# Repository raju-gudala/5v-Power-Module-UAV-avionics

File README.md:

# 5V Power Module for UAV Avionics

High-efficiency, wide-input 5V DC-DC power module designed for UAV avionics, supporting 3S–12S LiPo battery input using the LT8645SHV-2 synchronous buck converter.

## Overview

Flight-critical avionics — flight controllers, GPS, telemetry modules, and onboard sensors — need clean, stable power regardless of battery state or LiPo cell count. This module was designed to deliver a regulated 5V rail across a wide input range, with protection and monitoring features built in to keep avionics powered reliably through the full flight envelope.

## Key Features

- **Wide input range** — supports 3S–12S LiPo battery configurations
- **High-efficiency conversion** — built around the LT8645SHV-2 synchronous buck converter
- **Reverse-polarity protection** — prevents damage from incorrect battery connection
- **Under-voltage lockout (UVLO)** — disables output below a safe input threshold
- **Soft-start** — controlled ramp-up to avoid inrush current stress
- **Power-good monitoring** — provides a status signal for downstream system health checks
- **Low-EMI, low-ripple layout** — optimized PCB layout to minimize output ripple and electromagnetic interference
- **Thermal optimization** — layout tuned for improved thermal performance under sustained load

## Design Details

| Parameter | Value |
|---|---|
| Input voltage range | 3S–12S LiPo (~11.1V–50.4V) |
| Output voltage | 5V regulated |
| Converter IC | LT8645SHV-2 (synchronous buck) |
| Protection | Reverse-polarity, UVLO, soft-start |
| Monitoring | Power-good signal |
| Target loads | Flight controller, GPS, telemetry, onboard sensors |

## Tools Used

- **KiCad** — schematic capture and PCB layout
- **LTspice** — circuit simulation and power stage verification

## Design Process

1. Schematic capture around the LT8645SHV-2 buck converter topology
2. Component selection for wide input range and target efficiency
3. LTspice simulation to verify power stage behavior, ripple, and transient response
4. PCB layout optimized for low EMI, low output ripple, and thermal performance
5. Protection circuit integration (reverse-polarity, UVLO, soft-start, power-good)

## Repository Contents

```
├── schematics/     # KiCad schematic files
├── pcb/             # KiCad PCB layout files
├── simulation/      # LTspice simulation files
├── gerbers/          # Fabrication-ready Gerber files
└── docs/             # Datasheets, design notes, test results
```

*(Adjust the folder structure above to match what you actually push.)*

## Status

Designed as part of UAV avionics hardware development at TiHAN-IIT Hyderabad.

## Contact

- **Raju Gudala**
- Email: rajugudala730@gmail.com
- LinkedIn: [raju-gudala](https://www.linkedin.com/in/raju-gudala)
- Portfolio: [raju-gudala.github.io](https://raju-gudala.github.io/)

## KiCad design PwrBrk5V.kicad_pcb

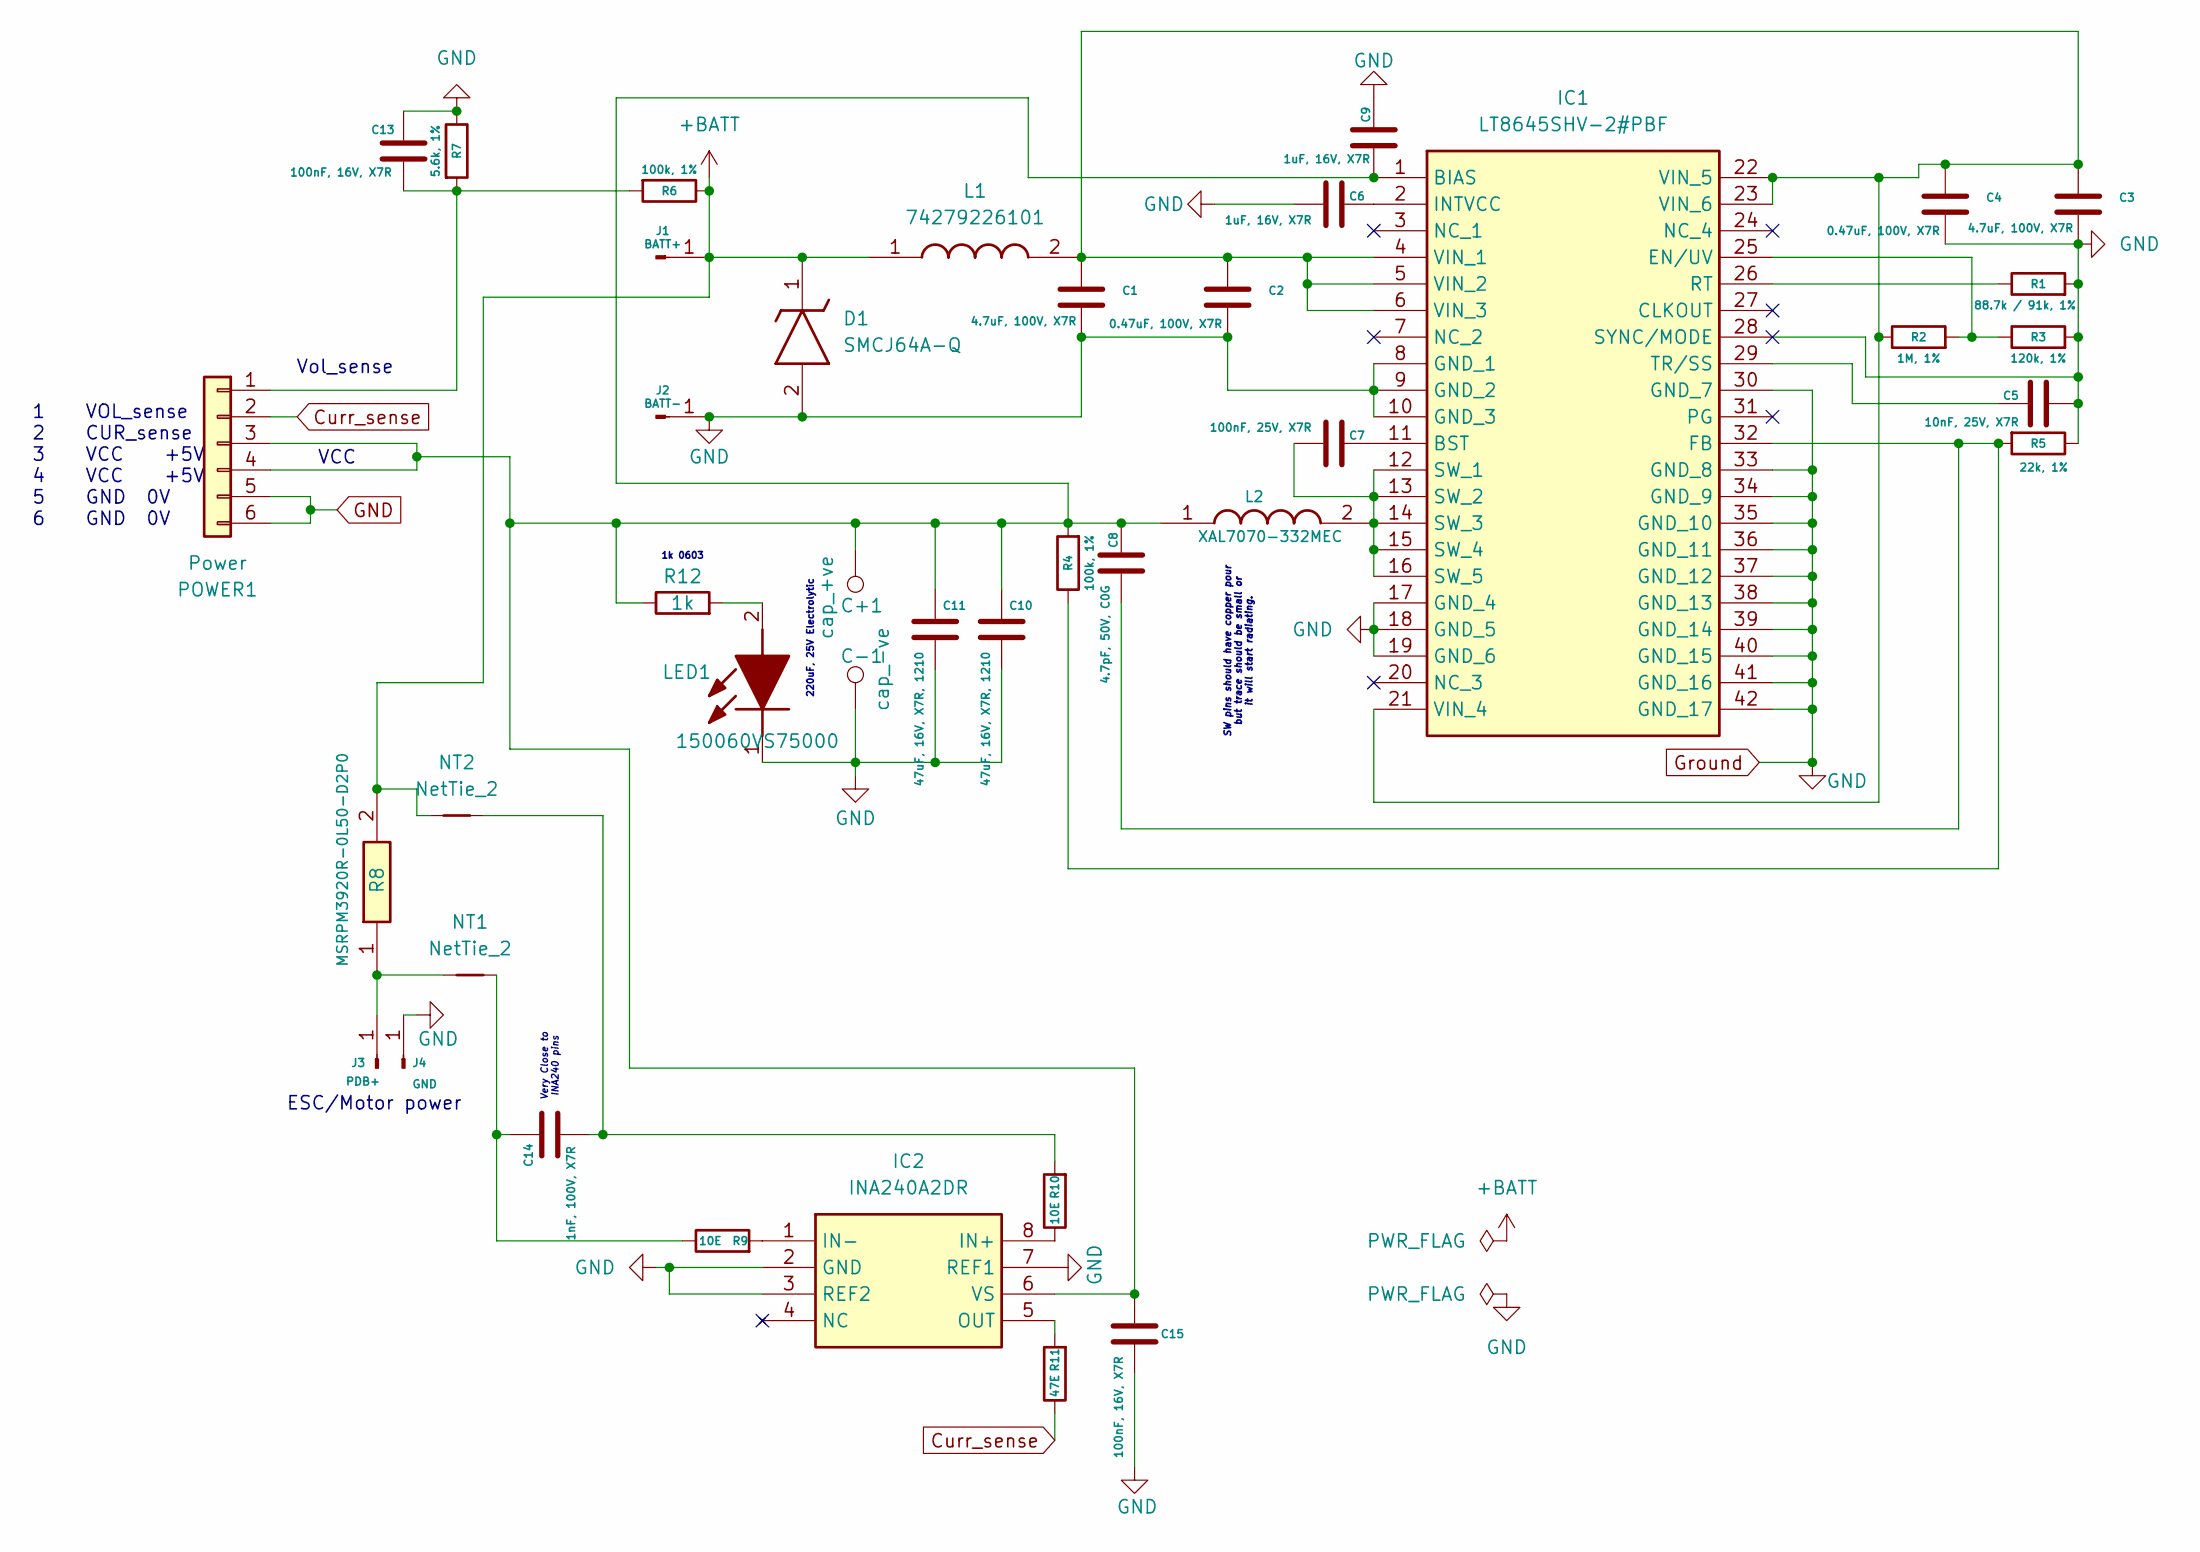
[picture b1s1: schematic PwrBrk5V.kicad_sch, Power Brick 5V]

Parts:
C1, C3: 4.7uF, 100V, X7R; C_1210_3225Metric
C2, C4: 0.47uF, 100V, X7R; C_0805_2012Metric
C5: 10nF, 25V, X7R; C_0603_1608Metric
C6, C9: 1uF, 16V, X7R; C_0603_1608Metric
C7: 100nF, 25V, X7R; C_0603_1608Metric
C8: 4.7pF, 50V, C0G; C_0603_1608Metric
C10, C11: 47uF, 16V, X7R, 1210; C_1210_3225Metric
C13: 100nF, 16V, X7R; R_0603_1608Metric
C14: 1nF, 100V, X7R; C_0603_1608Metric
C15: 100nF, 16V, X7R; C_0603_1608Metric
C+1: cap_+ve; solder_pad_2.5mmx2.5mm
C-1: cap_-ve; solder_pad_2.5mmx2.5mm
D1: SMCJ64A-Q; DIOM7959X262N; Mouser Part Number 652-SMCJ64A-Q
IC1: LT8645SHV-2#PBF; LT8645SHV2PBF; Mouser Part Number 584-LT8645SHV-2#PBF
IC2: INA240A2DR; SOIC127P600X175-8N; Mouser Part Number 595-INA240A2DR
J1: BATT+; pad 7mmx7mm
J2: BATT-; pad 7mmx7mm
J3: PDB+; pad 7mmx7mm
J4: GND; pad 7mmx7mm
L1: 74279226101; WE-MPSB_181252; Mouser Part Number 710-74279226101
L2: XAL7070-332MEC; XAL7070332MEC; Mouser Part Number 994-XAL7070-332MEC
LED1: 150060VS75000; LEDC1608X70N; Mouser Part Number 710-150060VS75000
NT1, NT2: NetTie_2; NetTie-2_SMD_Pad0.5mm
POWER1: Power; SM06B-GHS-TB
R1: 88.7k / 91k, 1%; R_0603_1608Metric
R2: 1M, 1%; R_0603_1608Metric
R3: 120k, 1%; R_0603_1608Metric
R4: 100k, 1%; R_0603_1608Metric
R5: 22k, 1%; R_0603_1608Metric
R6: 100k, 1%; R_0805_2012Metric
R7: 5.6k, 1%; R_0603_1608Metric
R8: MSRPM3920R-0L50-D2P0; MSRPM3920R0L50D2P0; Manufacturer_Part_Number MSRPM3920R-0L50-D2P0
R9, R10: 10E; R_0603_1608Metric
R11: 47E; R_0603_1608Metric
R12: 1k; R_0603_1608Metric

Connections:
+BATT: D1.1 (K), J1.1 (Pin_1_1), L1.1, NT2.1, R6.1, R8.2
Curr_sense: POWER1.2, R11.1
GND: C1.2, C2.2, C3.2, C4.2, C5.2, C6.1, C9.2, C10.1, C11.1, C13.2, C15.1, C-1.1 (1_1), D1.2 (A), IC1.8 (GND_1), IC1.9 (GND_2), IC1.10 (GND_3), IC1.17 (GND_4), IC1.18 (GND_5), IC1.19 (GND_6), IC1.28 (SYNC/MODE), IC1.30 (GND_7), IC1.33 (GND_8), IC1.34 (GND_9), IC1.35 (GND_10), IC1.36 (GND_11), IC1.37 (GND_12), IC1.38 (GND_13), IC1.39 (GND_14), IC1.40 (GND_15), IC1.41 (GND_16), IC1.42 (GND_17), IC2.2 (GND), IC2.3 (REF2), IC2.7 (REF1), J2.1 (Pin_1_1), J4.1 (Pin_1_1), LED1.1 (K), POWER1.5, POWER1.6, R1.2, R3.2, R5.1, R7.1
unnamed: C14.1, NT2.2, R10.2
unnamed: C14.2, NT1.2, R9.1
unnamed: C8.2, C9.1, C10.2, C11.2, C15.2, C+1.1 (1_1), IC1.1 (BIAS), IC2.6 (VS), L2.1, POWER1.3, POWER1.4, R4.2, R12.1
unnamed: C7.2, IC1.11 (BST)
unnamed: IC1.25 (EN/UV), R2.2, R3.1
unnamed: C8.1, IC1.32 (FB), R4.1, R5.2
unnamed: C6.2, IC1.2 (INTVCC)
unnamed: IC1.26 (RT), R1.1
unnamed: C7.1, IC1.12 (SW_1), IC1.13 (SW_2), IC1.14 (SW_3), IC1.15 (SW_4), IC1.16 (SW_5), L2.2
unnamed: C5.1, IC1.29 (TR/SS)
unnamed: C1.1, C2.1, C3.1, C4.1, IC1.4 (VIN_1), IC1.5 (VIN_2), IC1.6 (VIN_3), IC1.21 (VIN_4), IC1.22 (VIN_5), IC1.23 (VIN_6), L1.2, R2.1
unnamed: IC2.8 (IN+), R10.1
unnamed: IC2.1 (IN-), R9.2
unnamed: IC2.5 (OUT), R11.2
unnamed: J3.1 (Pin_1_1), NT1.1, R8.1
unnamed: LED1.2 (A), R12.2
unnamed: C13.1, POWER1.1, R6.2, R7.2

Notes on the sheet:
1k 0603
SW pins should have copper pour but trace should be small or it will start radiating.
1 VOL_sense 2 CUR_sense 3 VCC +5V 4 VCC +5V 5 GND 0V 6 GND 0V
220uF, 25V Electrolytic
ESC/Motor power
VCC
Vol_sense
Very Close to INA240 pins

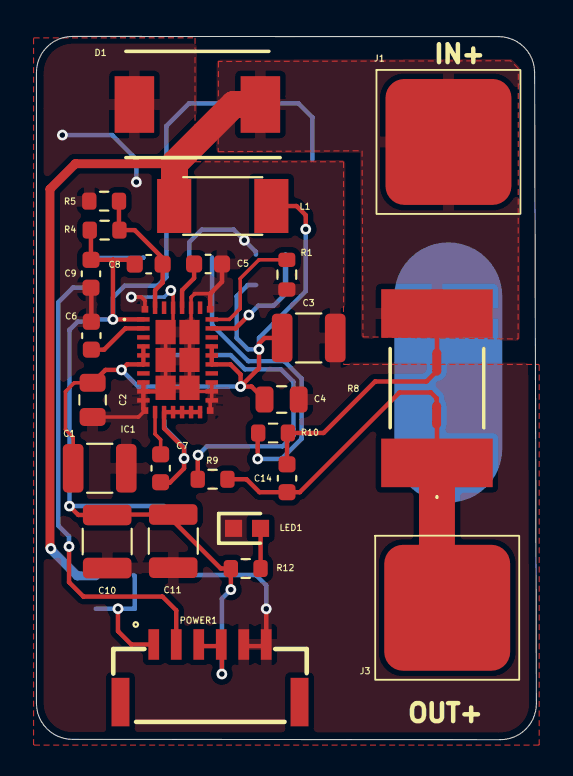
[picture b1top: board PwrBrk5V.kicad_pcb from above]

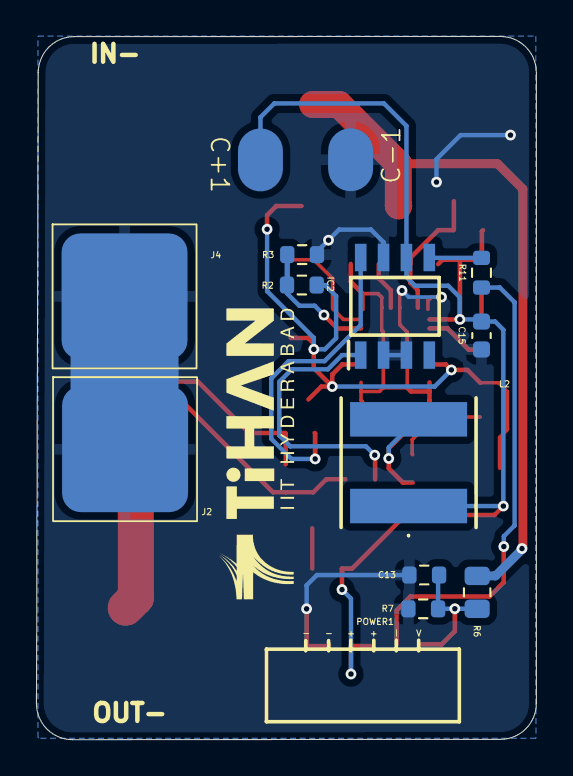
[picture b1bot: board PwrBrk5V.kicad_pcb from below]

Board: 2 copper layers, 27.8 x 39.1 mm, 41 parts (13 on the bottom side), 20 nets.
